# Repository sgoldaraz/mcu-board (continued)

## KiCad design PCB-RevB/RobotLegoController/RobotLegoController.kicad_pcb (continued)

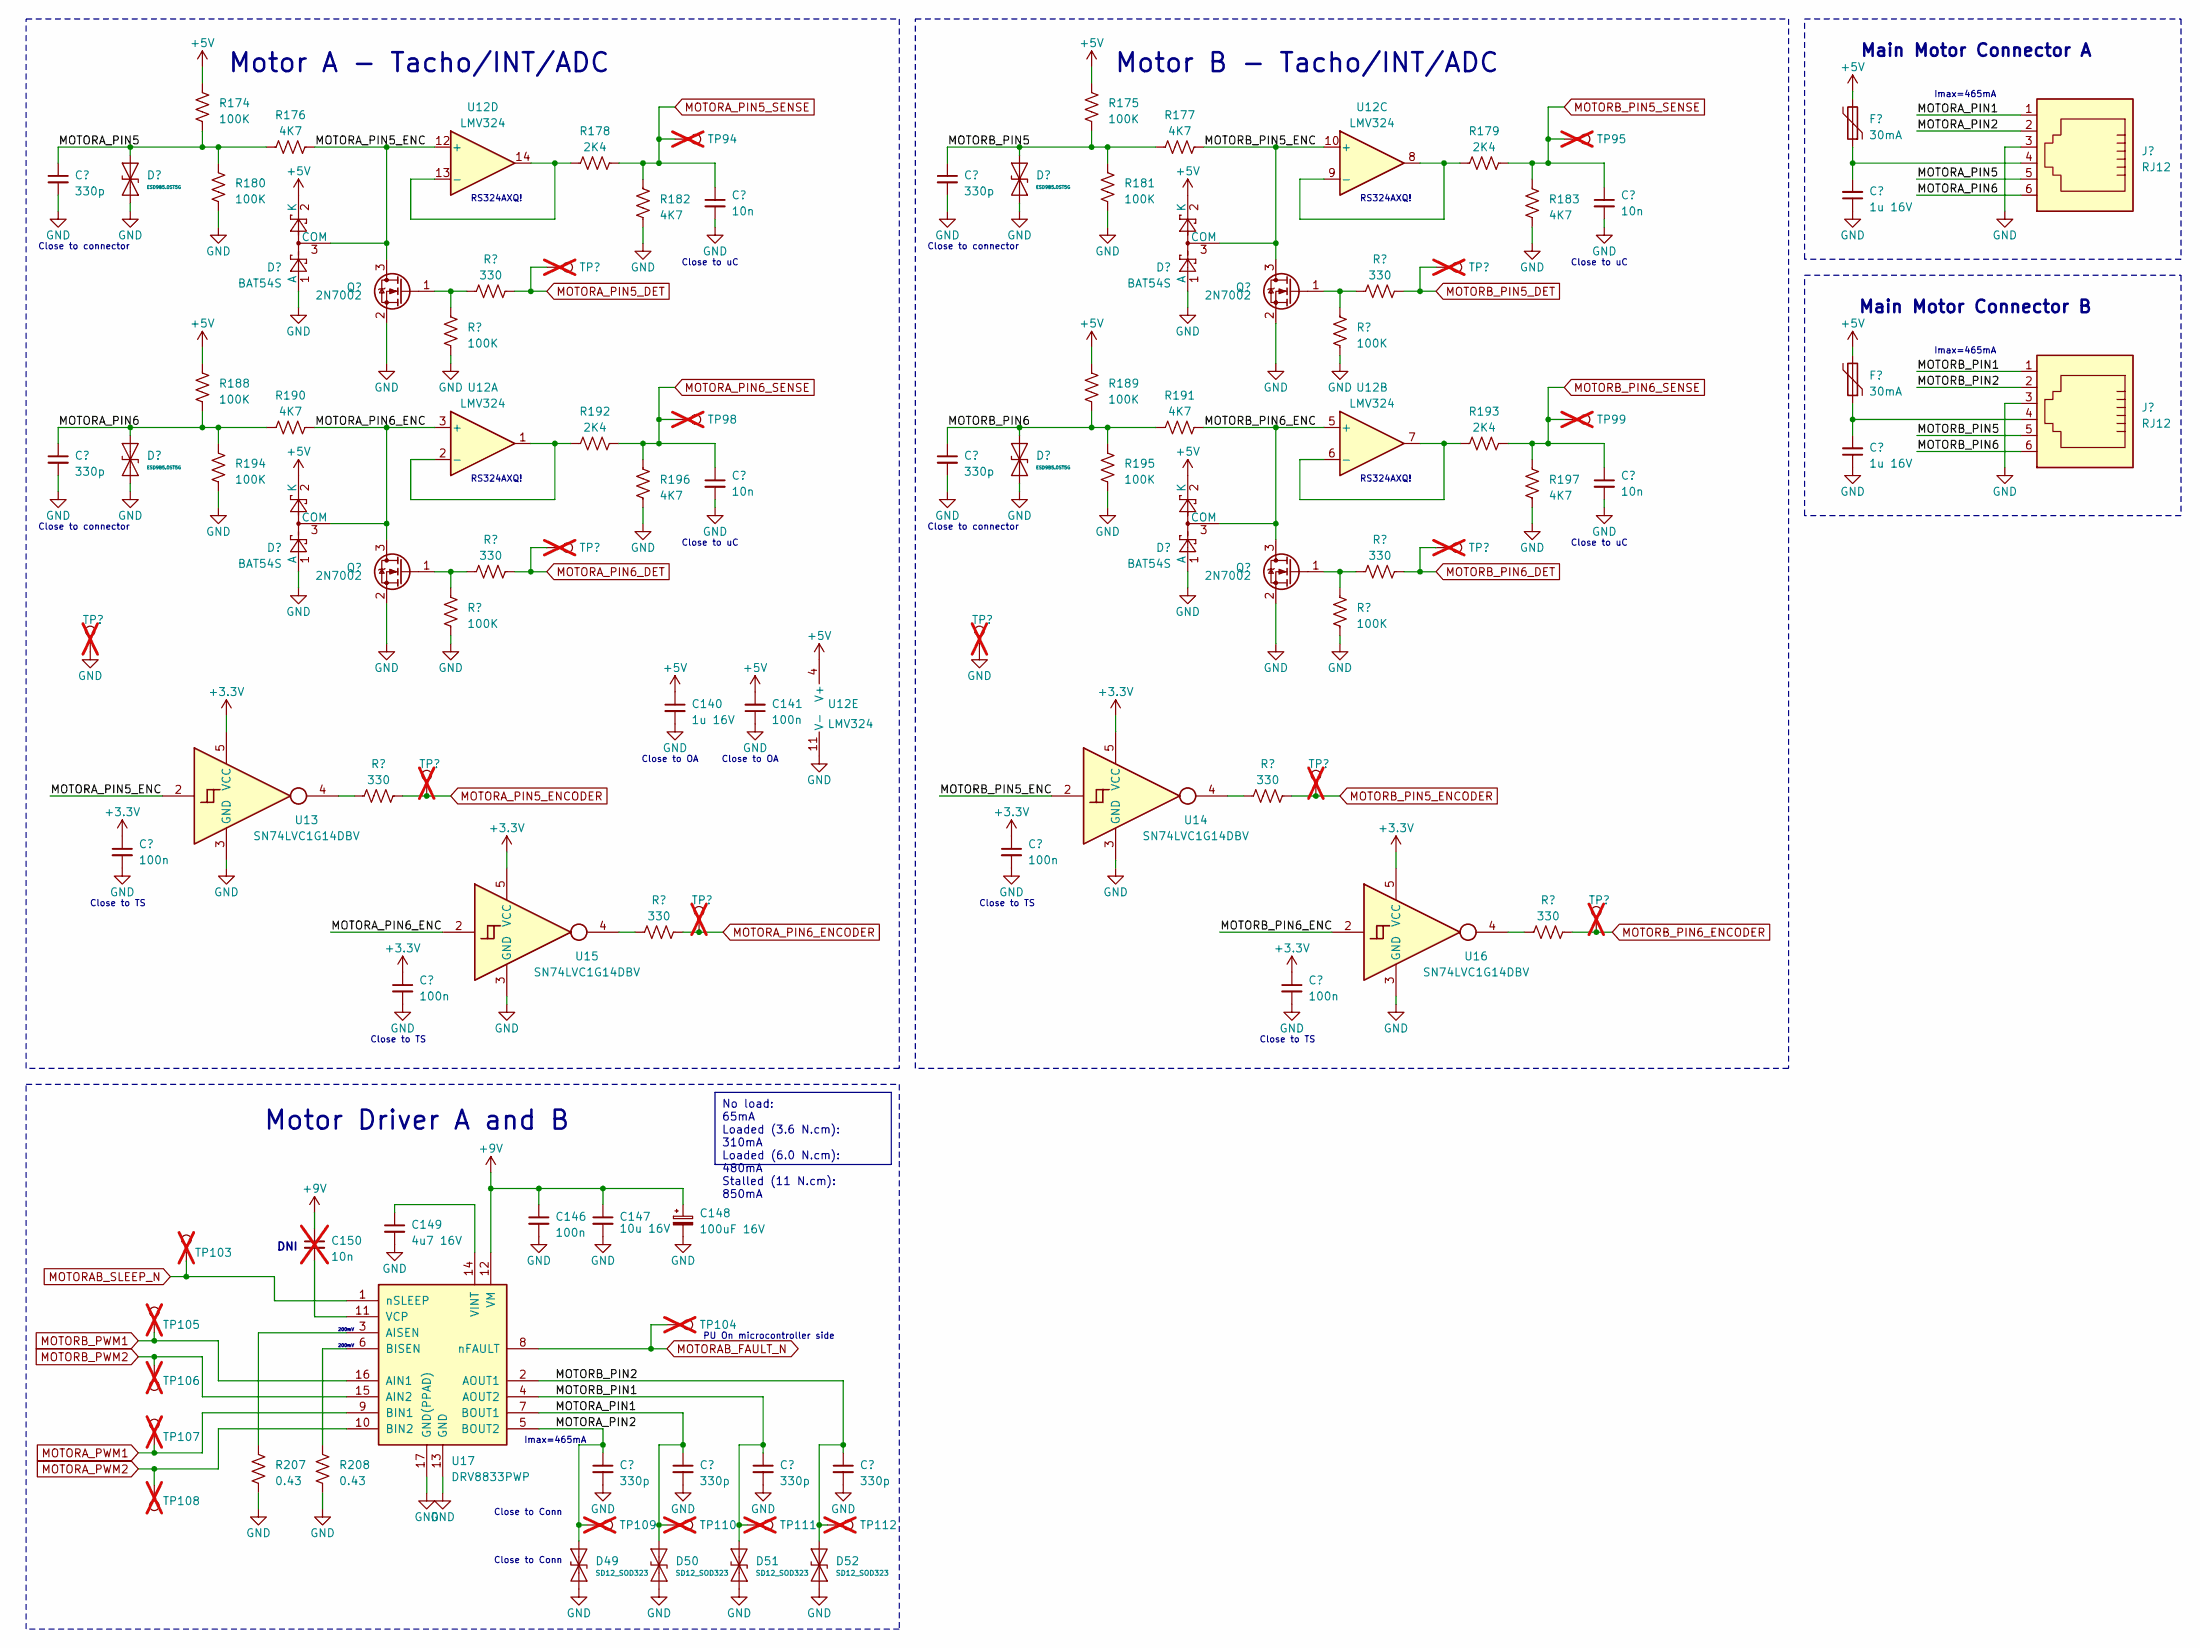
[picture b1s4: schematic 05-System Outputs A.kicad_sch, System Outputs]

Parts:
C118: 10n; C_0402_1005Metric
C130, C131, C136, C137, C151, C152, C153, C154: 330p; C_0402_1005Metric
C132, C135, C140: 1u 16V; C_0603_1608Metric
C141, C142, C143, C144, C145, C146: 100n; C_0402_1005Metric
C147: 10u 16V; C_0805_2012Metric
C148: 100uF 16V; CP_Elec_6.3x5.2
C149: 4u7 16V; C_0603_1608Metric
C150: 10n; C_0402_1005Metric; not fitted
D41, D42, D45, D46: ESD9B5.0ST5G; D_SOD-923
D43, D44, D47, D48: BAT54S; SOT-23
D49, D50, D51, D52: SD12_SOD323; D_SOD-323
F7, F8: 30mA; R_0603_1608Metric
J11, J12: RJ12; RJ12_Amphenol_54601
Q29, Q30, Q31, Q32: 2N7002; SOT-23
R174, R175, R180, R181, R186, R187, R188, R189, R194, R195, R200, R201: 100K; R_0402_1005Metric
R176, R177, R182, R183, R190, R191, R196, R197: 4K7; R_0402_1005Metric
R178, R179, R192, R193: 2K4; R_0402_1005Metric
R184, R185, R198, R199, R202, R203, R204, R205: 330; R_0402_1005Metric
R207, R208: 0.43; R_0805_2012Metric
TP16, TP20, TP94, TP95, TP96, TP97, TP98, TP99, TP100, TP101, TP103, TP104, TP105, TP106, TP107, TP108, TP109, TP110, TP111, TP112, TP134, TP135, TP142, TP143: S1mm; TestPoint_Pad_1.0x1.0mm; not fitted
U12: LMV324; SOIC-14_3.9x8.7mm_P1.27mm
U13, U14, U15, U16: SN74LVC1G14DBV; SOT-23-5
U17: DRV8833PWP; HTSSOP-16-1EP_4.4x5mm_P0.65mm_EP3.4x5mm_Mask2.46x2.31mm_The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

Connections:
+3.3V: C142.1, C143.1, C144.1, C145.1, U13.5 (VCC), U14.5 (VCC), U15.5 (VCC), U16.5 (VCC); also elsewhere on the board
+5V: C140.1, C141.2, D43.2 (K), D44.2 (K), D47.2 (K), D48.2 (K), F7.2, F8.2, R174.2, R175.2, R188.2, R189.2, U12.4 (V+); also elsewhere on the board
+9V: C146.1, C147.1, C148.1, C150.1, U17.12 (VM); also elsewhere on the board
/05-System Outputs A/MOTORA_PIN1: C152.1, D50.2 (A2), J11.1, TP110.1, U17.7 (BOUT1)
/05-System Outputs A/MOTORA_PIN2: C151.1, D49.2 (A2), J11.2, TP109.1, U17.5 (BOUT2)
/05-System Outputs A/MOTORA_PIN5: C130.1, D41.2 (A2), J11.5, R174.1, R176.2, R180.2; also elsewhere on the board
/05-System Outputs A/MOTORA_PIN6: C136.1, D45.2 (A2), J11.6, R188.1, R190.2, R194.2; also elsewhere on the board
/05-System Outputs A/MOTORB_PIN1: C153.1, D51.2 (A2), J12.1, TP111.1, U17.4 (AOUT2)
/05-System Outputs A/MOTORB_PIN2: C154.1, D52.2 (A2), J12.2, TP112.1, U17.2 (AOUT1)
/05-System Outputs A/MOTORB_PIN5: C131.1, D42.2 (A2), J12.5, R175.1, R177.2, R181.2; also elsewhere on the board
/05-System Outputs A/MOTORB_PIN6: C137.1, D46.2 (A2), J12.6, R189.1, R191.2, R195.2; also elsewhere on the board
GND: C118.2, C130.2, C131.2, C132.1, C135.1, C136.2, C137.2, C140.2, C141.1, C142.2, C143.2, C144.2, C145.2, C146.2, C147.2, C148.2, C149.2, C151.2, C152.2, C153.2, C154.2, D41.1 (A1), D42.1 (A1), D43.1 (A), D44.1 (A), D45.1 (A1), D46.1 (A1), D47.1 (A), D48.1 (A), D49.1 (A1), D50.1 (A1), D51.1 (A1), D52.1 (A1), J11.3, J12.3, Q29.2 (S), Q30.2 (S), Q31.2 (S), Q32.2 (S), R180.1, R181.1, R182.2, R183.2, R186.1, R187.1, R194.1, R195.1, R196.2, R197.2, R200.1, R201.1, R207.1, R208.1, TP142.1, TP143.1, U12.11 (V-), U13.3 (GND), U14.3 (GND), U15.3 (GND), U16.3 (GND), U17.13 (GND), U17.17 (GND(PPAD)); also elsewhere on the board
MOTORAB_FAULT_N: TP104.1, U17.8 (nFAULT); also elsewhere on the board
MOTORAB_SLEEP_N: TP103.1, U17.1 (nSLEEP); also elsewhere on the board
MOTORA_PIN5_DET: R184.1, TP96.1; also elsewhere on the board
MOTORA_PIN5_ENCODER: R202.1, TP134.1; also elsewhere on the board
MOTORA_PIN6_DET: R198.1, TP100.1; also elsewhere on the board
MOTORA_PIN6_ENCODER: R204.1, TP135.1; also elsewhere on the board
MOTORA_PWM1: TP107.1, U17.9 (BIN1); also elsewhere on the board
MOTORA_PWM2: TP108.1, U17.10 (BIN2); also elsewhere on the board
MOTORB_PIN5_DET: R185.1, TP97.1; also elsewhere on the board
MOTORB_PIN5_ENCODER: R203.1, TP16.1; also elsewhere on the board
MOTORB_PIN6_DET: R199.1, TP101.1; also elsewhere on the board
MOTORB_PIN6_ENCODER: R205.1, TP20.1; also elsewhere on the board
MOTORB_PWM1: TP105.1, U17.16 (AIN1); also elsewhere on the board
MOTORB_PWM2: TP106.1, U17.15 (AIN2); also elsewhere on the board
unnamed: C132.2, F7.1, J11.4
unnamed: C135.2, F8.1, J12.4
unnamed: Q29.1 (G), R184.2, R186.2
unnamed: Q30.1 (G), R185.2, R187.2
unnamed: Q31.1 (G), R198.2, R200.2
unnamed: Q32.1 (G), R199.2, R201.2
unnamed: R202.2, U13.4
unnamed: R203.2, U14.4
unnamed: R204.2, U15.4
unnamed: R205.2, U16.4
unnamed: R192.1, U12.1, U12.2 (-)
unnamed: R193.1, U12.6 (-), U12.7
unnamed: R179.1, U12.8, U12.9 (-)
unnamed: R178.1, U12.13 (-), U12.14
unnamed: R207.2, U17.3 (AISEN)
unnamed: R208.2, U17.6 (BISEN)
unnamed: C150.2, U17.11 (VCP)
unnamed: C149.1, U17.14 (VINT)

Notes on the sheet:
No load: 65mA Loaded (3.6 N.cm): 310mA Loaded (6.0 N.cm): 480mA Stalled (11 N.cm): 850mA
RS324AXQ!
Motor A - Tacho/INT/ADC
Close to connector
Close to Conn
Close to uC
200mV
Close to TS
Main Motor Connector B
Motor Driver A and B
Imax=465mA
DNI
Main Motor Connector A
PU On microcontroller side
Close to OA
Motor B - Tacho/INT/ADC

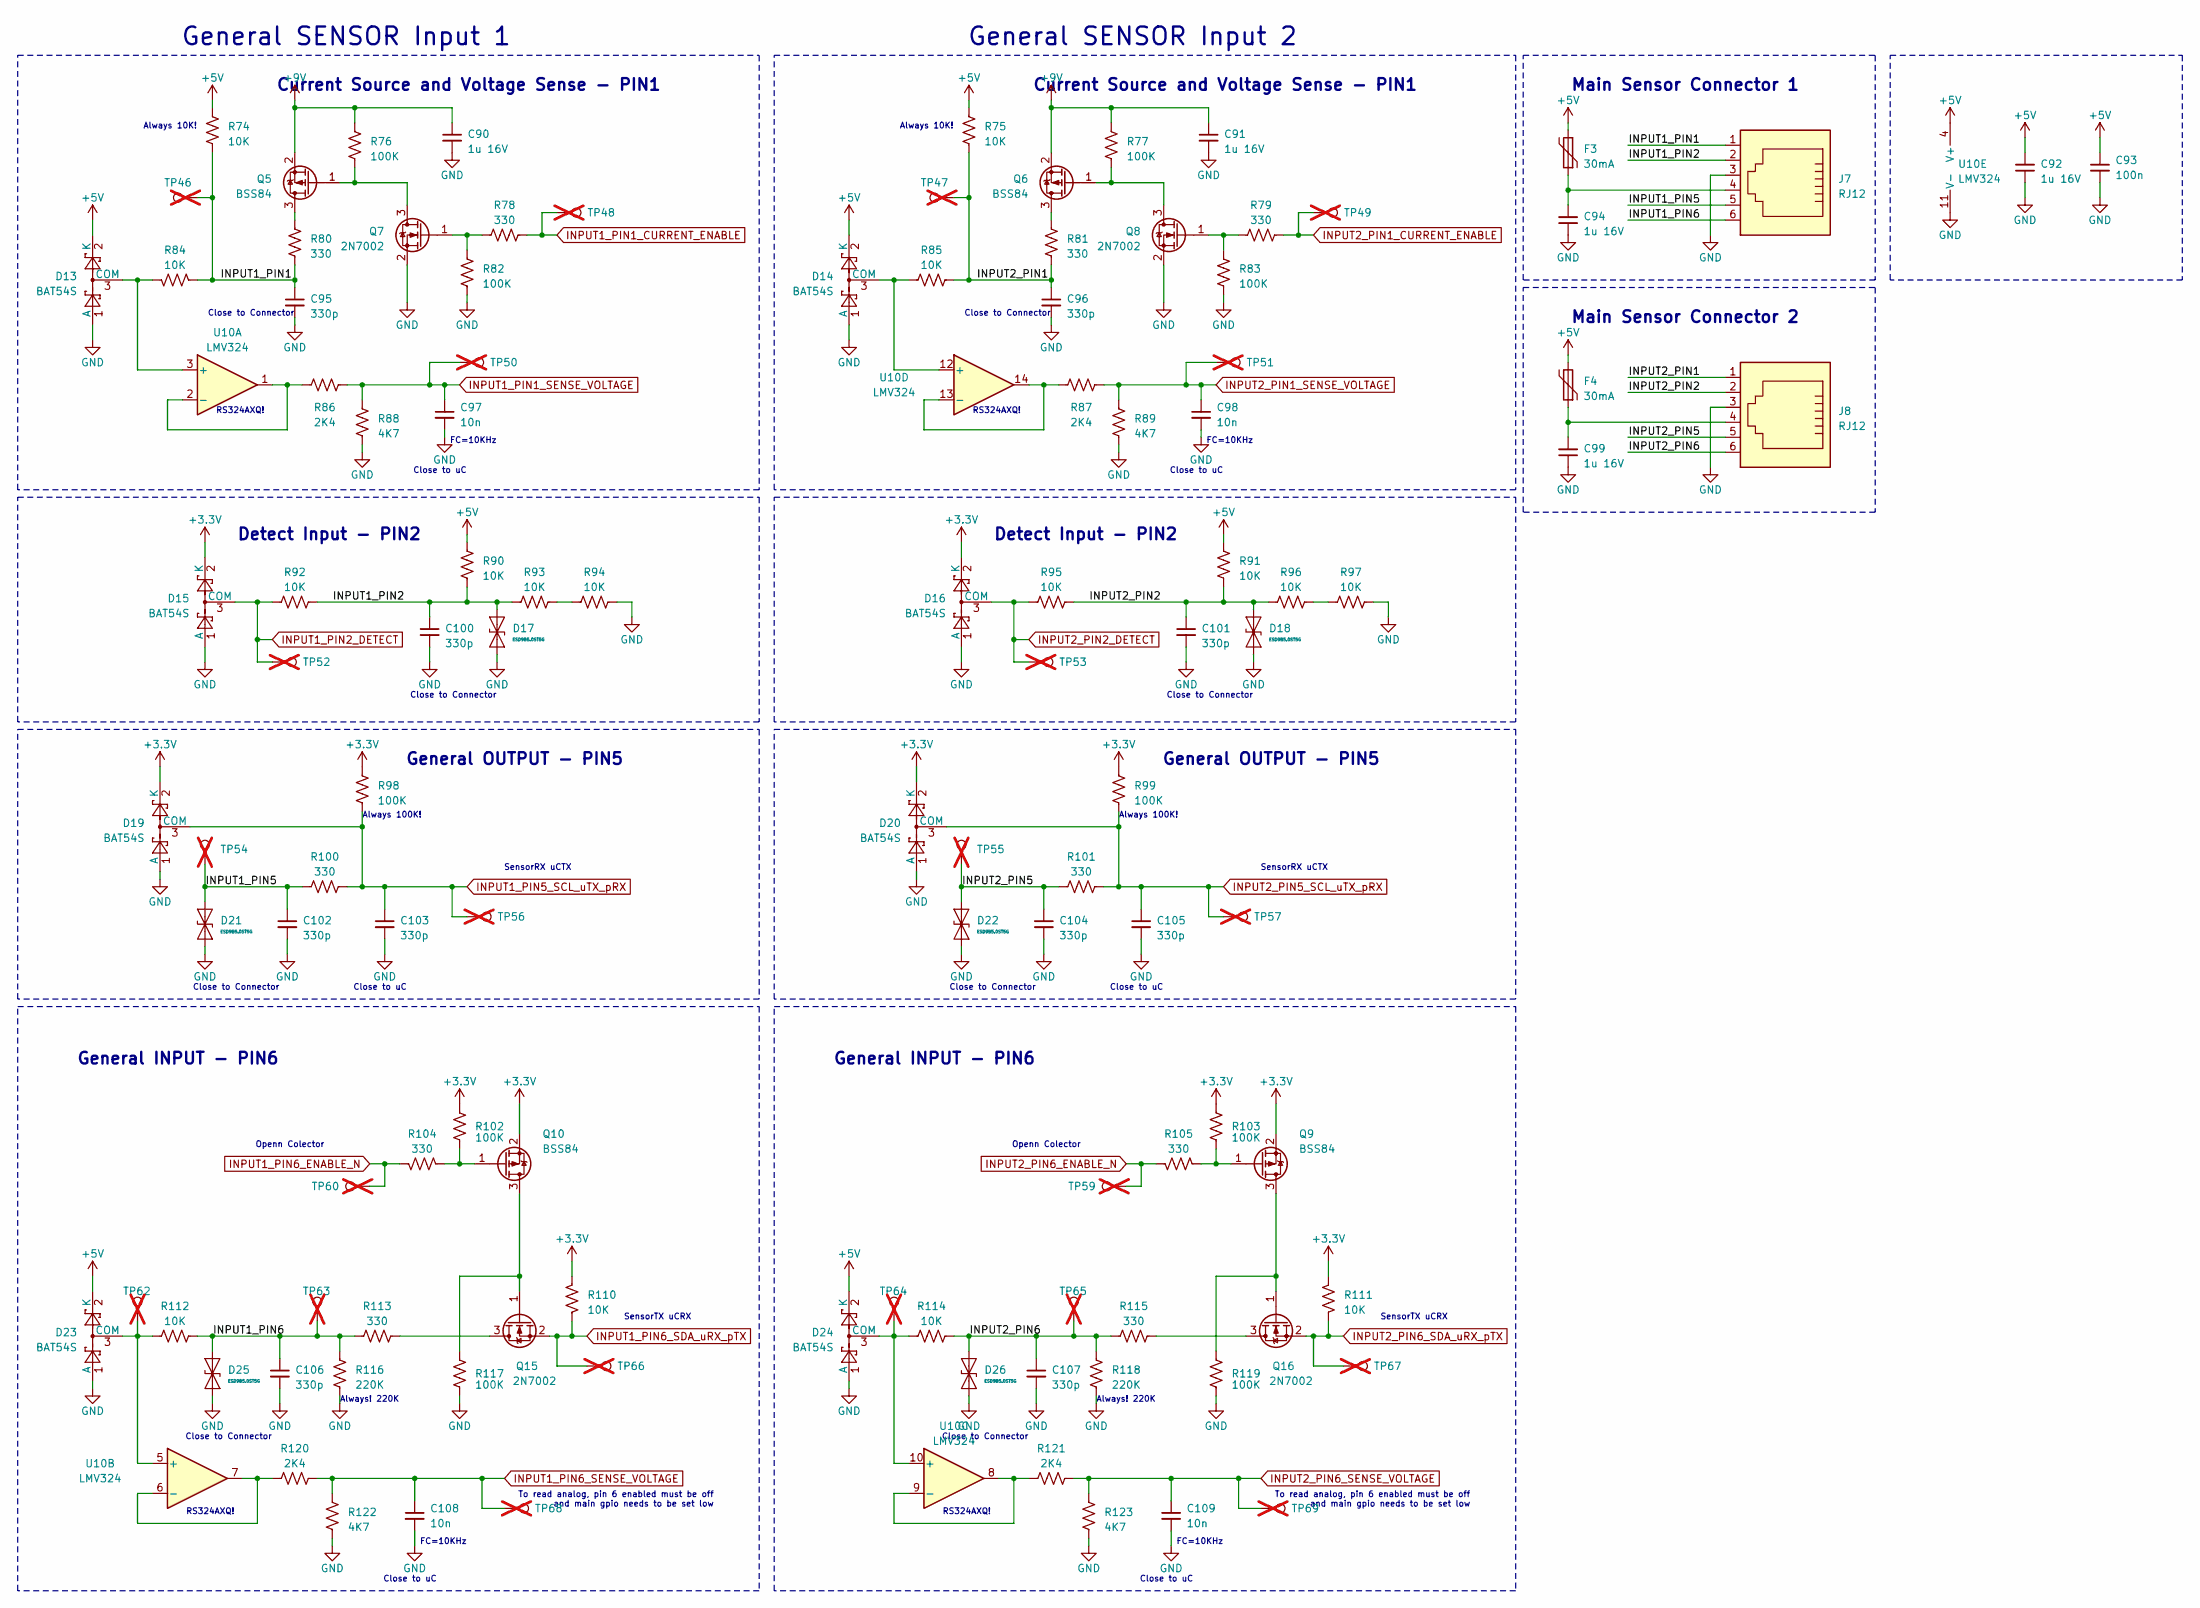
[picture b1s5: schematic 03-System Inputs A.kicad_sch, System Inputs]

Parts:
C90, C91, C92, C94, C99: 1u 16V; C_0603_1608Metric
C93: 100n; C_0402_1005Metric
C95, C96, C100, C101, C102, C103, C104, C105, C106, C107: 330p; C_0402_1005Metric
C97, C98, C108, C109: 10n; C_0402_1005Metric
D13, D14, D15, D16, D19, D20, D23, D24: BAT54S; SOT-23
D17, D18, D21, D22, D25, D26: ESD9B5.0ST5G; D_SOD-923
F3, F4: 30mA; R_0603_1608Metric
J7, J8: RJ12; RJ25_Wayconn_MJEA-660X1_Horizontal
Q5, Q6, Q9, Q10: BSS84; SOT-23
Q7, Q8, Q15, Q16: 2N7002; SOT-23
R74, R75, R84, R85, R90, R91, R92, R93, R94, R95, R96, R97, R110, R111, R112, R114: 10K; R_0402_1005Metric
R76, R77, R82, R83, R98, R99, R102, R103, R117, R119: 100K; R_0402_1005Metric
R78, R79, R80, R81, R100, R101, R104, R105, R113, R115: 330; R_0402_1005Metric
R86, R87, R120, R121: 2K4; R_0402_1005Metric
R88, R89, R122, R123: 4K7; R_0402_1005Metric
R116, R118: 220K; R_0402_1005Metric
TP46, TP47, TP48, TP49, TP50, TP51, TP52, TP53, TP54, TP55, TP56, TP57, TP59, TP60, TP62, TP63, TP64, TP65, TP66, TP67, TP68, TP69: S1mm; TestPoint_Pad_1.0x1.0mm; not fitted
U10: LMV324; SOIC-14_3.9x8.7mm_P1.27mm

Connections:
+3.3V: D15.2 (K), D16.2 (K), D19.2 (K), D20.2 (K), Q9.2 (S), Q10.2 (S), R98.2, R99.2, R102.2, R103.2, R110.1, R111.1; also elsewhere on the board
+5V: C92.2, C93.1, D13.2 (K), D14.2 (K), D23.2 (K), D24.2 (K), F3.2, F4.2, R74.2, R75.2, R90.2, R91.2, U10.4 (V+); also elsewhere on the board
+9V: C90.1, C91.1, Q5.2 (S), Q6.2 (S), R76.2, R77.2; also elsewhere on the board
/03-System Inputs A/INPUT1_PIN1: C95.1, J7.1, R74.1, R80.1, R84.2, TP46.1
/03-System Inputs A/INPUT1_PIN2: C100.1, D17.2 (A2), J7.2, R90.1, R92.2, R93.2
/03-System Inputs A/INPUT1_PIN5: C102.1, D21.2 (A2), J7.5, R100.2, TP54.1
/03-System Inputs A/INPUT1_PIN6: C106.1, D25.2 (A2), J7.6, R112.2, R113.2, R116.1, TP63.1
/03-System Inputs A/INPUT2_PIN1: C96.1, J8.1, R75.1, R81.1, R85.1, TP47.1
/03-System Inputs A/INPUT2_PIN2: C101.1, D18.2 (A2), J8.2, R91.1, R95.2, R96.2
/03-System Inputs A/INPUT2_PIN5: C104.1, D22.2 (A2), J8.5, R101.2, TP55.1
/03-System Inputs A/INPUT2_PIN6: C107.1, D26.2 (A2), J8.6, R114.2, R115.2, R118.1, TP65.1
GND: C90.2, C91.2, C92.1, C93.2, C94.1, C95.2, C96.2, C97.2, C98.2, C99.1, C100.2, C101.2, C102.2, C103.2, C104.2, C105.2, C106.2, C107.2, C108.2, C109.2, D13.1 (A), D14.1 (A), D15.1 (A), D16.1 (A), D17.1 (A1), D18.1 (A1), D19.1 (A), D20.1 (A), D21.1 (A1), D22.1 (A1), D23.1 (A), D24.1 (A), D25.1 (A1), D26.1 (A1), J7.3, J8.3, Q7.2 (S), Q8.2 (S), R82.1, R83.1, R88.2, R89.2, R94.1, R97.1, R116.2, R117.1, R118.2, R119.1, R122.2, R123.2, U10.11 (V-); also elsewhere on the board
INPUT1_PIN1_CURRENT_ENABLE: R78.1, TP48.1; also elsewhere on the board
INPUT1_PIN1_SENSE_VOLTAGE: C97.1, R86.2, R88.1, TP50.1; also elsewhere on the board
INPUT1_PIN2_DETECT: D15.3 (COM), R92.1, TP52.1; also elsewhere on the board
INPUT1_PIN5_SCL_uTX_pRX: C103.1, D19.3 (COM), R98.1, R100.1, TP56.1; also elsewhere on the board
INPUT1_PIN6_ENABLE_N: R104.1, TP60.1; also elsewhere on the board
INPUT1_PIN6_SDA_uRX_pTX: Q15.2 (S), R110.2, TP66.1; also elsewhere on the board
INPUT1_PIN6_SENSE_VOLTAGE: C108.1, R120.2, R122.1, TP68.1; also elsewhere on the board
INPUT2_PIN1_CURRENT_ENABLE: R79.1, TP49.1; also elsewhere on the board
INPUT2_PIN1_SENSE_VOLTAGE: C98.1, R87.2, R89.1, TP51.1; also elsewhere on the board
INPUT2_PIN2_DETECT: D16.3 (COM), R95.1, TP53.1; also elsewhere on the board
INPUT2_PIN5_SCL_uTX_pRX: C105.1, D20.3 (COM), R99.1, R101.1, TP57.1; also elsewhere on the board
INPUT2_PIN6_ENABLE_N: R105.1, TP59.1; also elsewhere on the board
INPUT2_PIN6_SDA_uRX_pTX: Q16.2 (S), R111.2, TP67.1; also elsewhere on the board
INPUT2_PIN6_SENSE_VOLTAGE: C109.1, R121.2, R123.1, TP69.1; also elsewhere on the board
unnamed: C94.2, F3.1, J7.4
unnamed: C99.2, F4.1, J8.4
unnamed: D13.3 (COM), R84.1, U10.3 (+)
unnamed: D14.3 (COM), R85.2, U10.12 (+)
unnamed: D23.3 (COM), R112.1, TP62.1, U10.5 (+)
unnamed: D24.3 (COM), R114.1, TP64.1, U10.10 (+)
unnamed: Q5.3 (D), R80.2
unnamed: Q5.1 (G), Q7.3 (D), R76.1
unnamed: Q6.3 (D), R81.2
unnamed: Q6.1 (G), Q8.3 (D), R77.1
unnamed: Q7.1 (G), R78.2, R82.2
unnamed: Q8.1 (G), R79.2, R83.2
unnamed: Q9.1 (G), R103.1, R105.2
unnamed: Q10.3 (D), Q15.1 (G), R117.2
unnamed: Q10.1 (G), R102.1, R104.2
unnamed: Q15.3 (D), R113.1
unnamed: Q16.3 (D), R115.1
unnamed: Q9.3 (D), Q16.1 (G), R119.2
unnamed: R93.1, R94.2
unnamed: R96.1, R97.2
unnamed: R86.1, U10.1, U10.2 (-)
unnamed: R120.1, U10.6 (-), U10.7
unnamed: R121.1, U10.8, U10.9 (-)
unnamed: R87.1, U10.13 (-), U10.14

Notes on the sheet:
RS324AXQ!
General OUTPUT - PIN5
Close to Connector
Main Sensor Connector 2
Close to uC
FC=10KHz
General SENSOR Input 2
Detect Input - PIN2
Main Sensor Connector 1
To read analog, pin 6 enabled must be off and main gpio needs to be set low
Openn Colector
Current Source and Voltage Sense - PIN1
Always 100K!
General SENSOR Input 1
General INPUT - PIN6
Always 10K!
SensorRX uCTX
Always! 220K
SensorTX uCRX

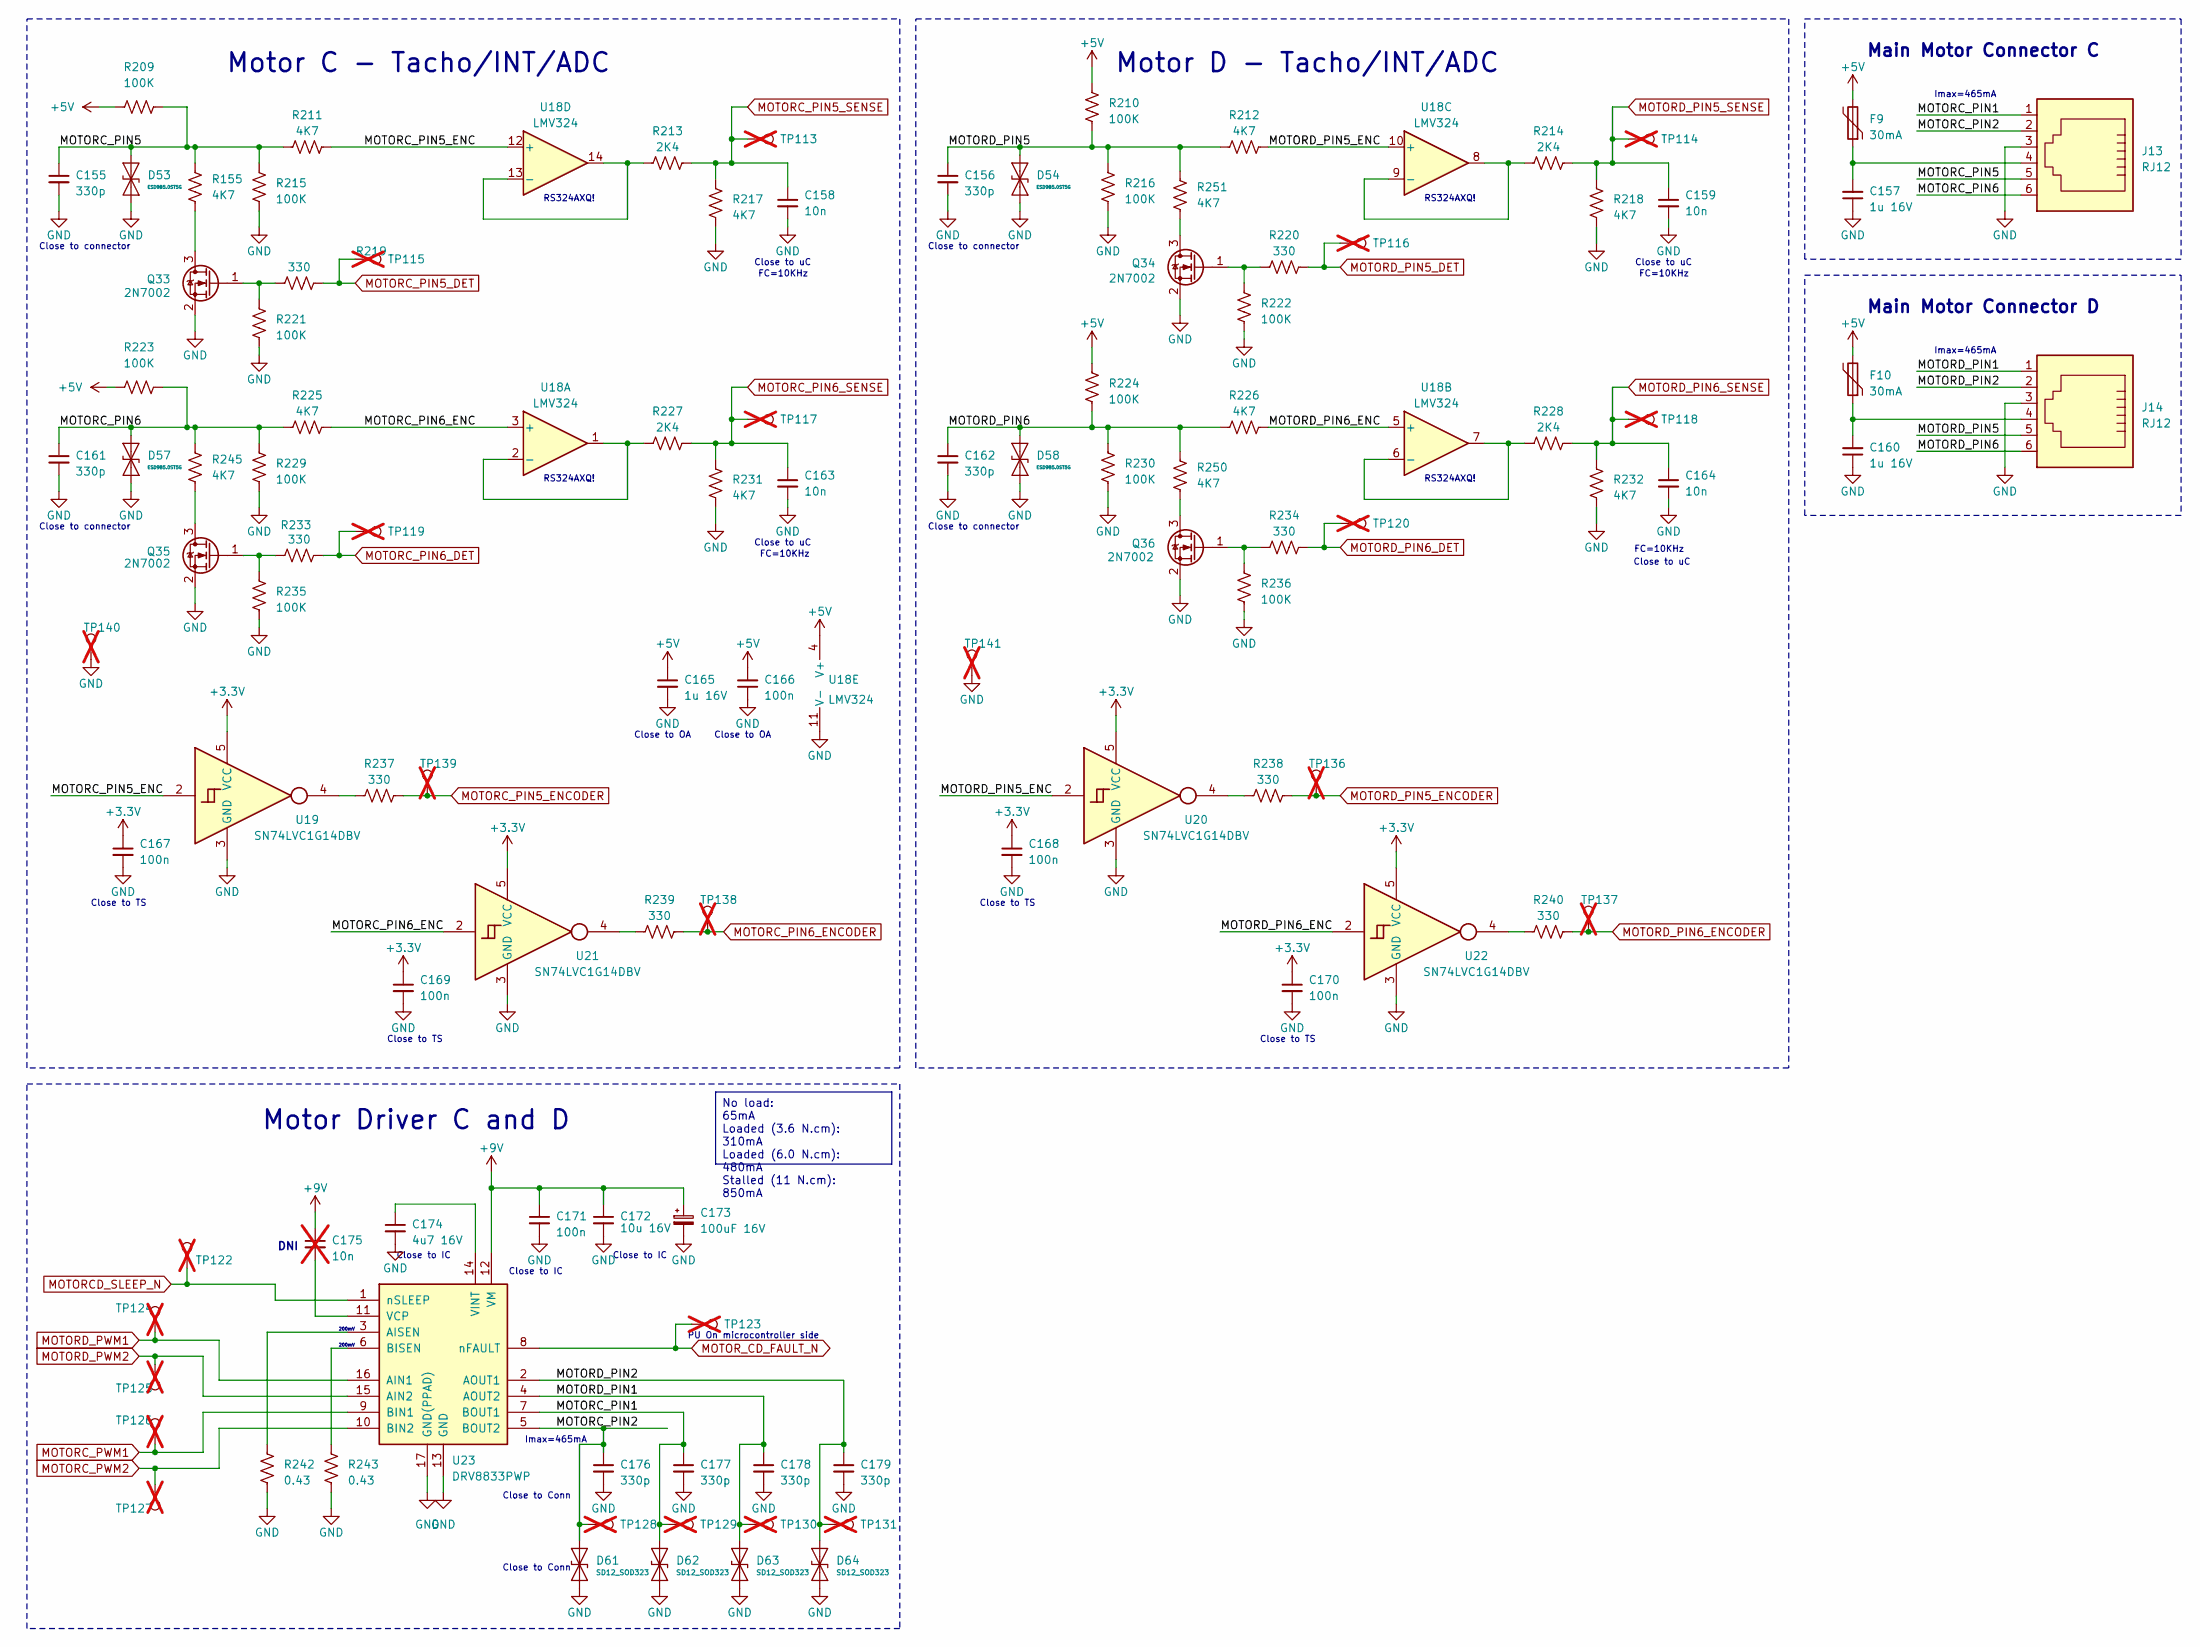
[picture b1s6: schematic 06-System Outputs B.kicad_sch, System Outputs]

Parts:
C155, C156, C161, C162, C176, C177, C178, C179: 330p; C_0402_1005Metric
C157, C160, C165: 1u 16V; C_0603_1608Metric
C158, C159, C163, C164: 10n; C_0402_1005Metric
C166, C167, C168, C169, C170, C171: 100n; C_0402_1005Metric
C172: 10u 16V; C_0805_2012Metric
C173: 100uF 16V; CP_Elec_6.3x5.2
C174: 4u7 16V; C_0603_1608Metric
C175: 10n; C_0402_1005Metric; not fitted
D53, D54, D57, D58: ESD9B5.0ST5G; D_SOD-923
D61, D62, D63, D64: SD12_SOD323; D_SOD-323
F9, F10: 30mA; R_0603_1608Metric
J13, J14: RJ12; RJ25_Wayconn_MJEA-660X1_Horizontal
Q33, Q34, Q35, Q36: 2N7002; SOT-23
R155, R211, R212, R217, R218, R225, R226, R231, R232, R245, R250, R251: 4K7; R_0402_1005Metric
R209, R210, R215, R216, R221, R222, R223, R224, R229, R230, R235, R236: 100K; R_0402_1005Metric
R213, R214, R227, R228: 2K4; R_0402_1005Metric
R219, R220, R233, R234, R237, R238, R239, R240: 330; R_0402_1005Metric
R242, R243: 0.43; R_0805_2012Metric
TP113, TP114, TP115, TP116, TP117, TP118, TP119, TP120, TP122, TP123, TP124, TP125, TP126, TP127, TP128, TP129, TP130, TP131, TP136, TP137, TP138, TP139, TP140, TP141: S1mm; TestPoint_Pad_1.0x1.0mm; not fitted
U18: LMV324; SOIC-14_3.9x8.7mm_P1.27mm
U19, U20, U21, U22: SN74LVC1G14DBV; SOT-23-5
U23: DRV8833PWP; HTSSOP-16-1EP_4.4x5mm_P0.65mm_EP3.4x5mm_Mask2.46x2.31mm_The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

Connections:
+3.3V: C167.1, C168.1, C169.1, C170.1, U19.5 (VCC), U20.5 (VCC), U21.5 (VCC), U22.5 (VCC); also elsewhere on the board
+5V: C165.1, C166.2, F9.2, F10.2, R209.2, R210.2, R223.2, R224.2, U18.4 (V+); also elsewhere on the board
+9V: C171.1, C172.1, C173.1, C175.1, U23.12 (VM); also elsewhere on the board
/06-System Outputs B/MOTORC_PIN1: C177.1, D62.2 (A2), J13.1, TP129.1, U23.7 (BOUT1)
/06-System Outputs B/MOTORC_PIN2: C176.1, D61.2 (A2), J13.2, TP128.1, U23.5 (BOUT2)
/06-System Outputs B/MOTORC_PIN5: C155.1, D53.2 (A2), J13.5, R155.1, R209.1, R211.2, R215.2
/06-System Outputs B/MOTORC_PIN5_ENC: R211.1, U18.12 (+), U19.2
/06-System Outputs B/MOTORC_PIN6: C161.1, D57.2 (A2), J13.6, R223.1, R225.2, R229.2, R245.1
/06-System Outputs B/MOTORC_PIN6_ENC: R225.1, U18.3 (+), U21.2
/06-System Outputs B/MOTORD_PIN1: C178.1, D63.2 (A2), J14.1, TP130.1, U23.4 (AOUT2)
/06-System Outputs B/MOTORD_PIN2: C179.1, D64.2 (A2), J14.2, TP131.1, U23.2 (AOUT1)
/06-System Outputs B/MOTORD_PIN5: C156.1, D54.2 (A2), J14.5, R210.1, R212.2, R216.2, R251.1
/06-System Outputs B/MOTORD_PIN5_ENC: R212.1, U18.10 (+), U20.2
/06-System Outputs B/MOTORD_PIN6: C162.1, D58.2 (A2), J14.6, R224.1, R226.2, R230.2, R250.1
/06-System Outputs B/MOTORD_PIN6_ENC: R226.1, U18.5 (+), U22.2
GND: C155.2, C156.2, C157.1, C158.2, C159.2, C160.1, C161.2, C162.2, C163.2, C164.2, C165.2, C166.1, C167.2, C168.2, C169.2, C170.2, C171.2, C172.2, C173.2, C174.2, C176.2, C177.2, C178.2, C179.2, D53.1 (A1), D54.1 (A1), D57.1 (A1), D58.1 (A1), D61.1 (A1), D62.1 (A1), D63.1 (A1), D64.1 (A1), J13.3, J14.3, Q33.2 (S), Q34.2 (S), Q35.2 (S), Q36.2 (S), R215.1, R216.1, R217.2, R218.2, R221.1, R222.1, R229.1, R230.1, R231.2, R232.2, R235.1, R236.1, R242.1, R243.1, TP140.1, TP141.1, U18.11 (V-), U19.3 (GND), U20.3 (GND), U21.3 (GND), U22.3 (GND), U23.13 (GND), U23.17 (GND(PPAD)); also elsewhere on the board
MOTORCD_SLEEP_N: TP122.1, U23.1 (nSLEEP); also elsewhere on the board
MOTORC_PIN5_DET: R219.1, TP115.1; also elsewhere on the board
MOTORC_PIN5_ENCODER: R237.1, TP139.1; also elsewhere on the board
MOTORC_PIN5_SENSE: C158.1, R213.2, R217.1, TP113.1; also elsewhere on the board
MOTORC_PIN6_DET: R233.1, TP119.1; also elsewhere on the board
MOTORC_PIN6_ENCODER: R239.1, TP138.1; also elsewhere on the board
MOTORC_PIN6_SENSE: C163.1, R227.2, R231.1, TP117.1; also elsewhere on the board
MOTORC_PWM1: TP126.1, U23.9 (BIN1); also elsewhere on the board
MOTORC_PWM2: TP127.1, U23.10 (BIN2); also elsewhere on the board
MOTORD_PIN5_DET: R220.1, TP116.1; also elsewhere on the board
MOTORD_PIN5_ENCODER: R238.1, TP136.1; also elsewhere on the board
MOTORD_PIN5_SENSE: C159.1, R214.2, R218.1, TP114.1; also elsewhere on the board
MOTORD_PIN6_DET: R234.1, TP120.1; also elsewhere on the board
MOTORD_PIN6_ENCODER: R240.1, TP137.1; also elsewhere on the board
MOTORD_PIN6_SENSE: C164.1, R228.2, R232.1, TP118.1; also elsewhere on the board
MOTORD_PWM1: TP124.1, U23.16 (AIN1); also elsewhere on the board
MOTORD_PWM2: TP125.1, U23.15 (AIN2); also elsewhere on the board
MOTOR_CD_FAULT_N: TP123.1, U23.8 (nFAULT); also elsewhere on the board
unnamed: C157.2, F9.1, J13.4
unnamed: C160.2, F10.1, J14.4
unnamed: Q33.3 (D), R155.2
unnamed: Q33.1 (G), R219.2, R221.2
unnamed: Q34.3 (D), R251.2
unnamed: Q34.1 (G), R220.2, R222.2
unnamed: Q35.3 (D), R245.2
unnamed: Q35.1 (G), R233.2, R235.2
unnamed: Q36.3 (D), R250.2
unnamed: Q36.1 (G), R234.2, R236.2
unnamed: R237.2, U19.4
unnamed: R238.2, U20.4
unnamed: R239.2, U21.4
unnamed: R240.2, U22.4
unnamed: R227.1, U18.1, U18.2 (-)
unnamed: R228.1, U18.6 (-), U18.7
unnamed: R214.1, U18.8, U18.9 (-)
unnamed: R213.1, U18.13 (-), U18.14
unnamed: R242.2, U23.3 (AISEN)
unnamed: R243.2, U23.6 (BISEN)
unnamed: C175.2, U23.11 (VCP)
unnamed: C174.1, U23.14 (VINT)

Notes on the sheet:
Close to IC
Close to TS
200mV
RS324AXQ!
Close to connector
Main Motor Connector D
FC=10KHz
Close to uC
Close to OA
Close to Conn
DNI
Motor C - Tacho/INT/ADC
Imax=465mA
Motor Driver C and D
PU On microcontroller side
Main Motor Connector C
Motor D - Tacho/INT/ADC
No load: 65mA Loaded (3.6 N.cm): 310mA Loaded (6.0 N.cm): 480mA Stalled (11 N.cm): 850mA
